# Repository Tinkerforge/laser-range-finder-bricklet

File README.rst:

Laser Range Finder Bricklet
===========================

This repository contains the firmware source code and the hardware design
files. The documentation generator configs can be found at
https://github.com/Tinkerforge/generators

Repository Content
------------------

software/:
 * examples/: Examples for all supported languages
 * build/: Compiled files
 * src/: Source code of firmware
 * Makefile: Makefile to build project

hardware/:
 * Contains KiCad project files and additionally schematics as PDF

datasheets/:
 * Contains datasheets for sensors and complex ICs that are used

Hardware
--------

The hardware is designed with the open source EDA Suite KiCad
(http://www.kicad.org). Before you are able to open the files,
you have to install the Tinkerforge kicad-libraries
(https://github.com/Tinkerforge/kicad-libraries). You can either clone
them directly in hardware/ or clone them in a separate folder and
symlink them into hardware/
(ln -s kicad_path/kicad-libraries project_path/hardware). After that you
can open the .pro file in hardware/ with KiCad and from there view and
modify the schematics and the PCB layout.

Software
--------

If you want to do your own Brick/Bricklet firmware development we highly
recommend that you use our build environment setup script and read the
tutorial (https://www.tinkerforge.com/en/doc/Tutorials/Tutorial_Build_Environment/Tutorial.html).

To compile the C code we recommend you to install the newest GNU Arm Embedded
Toolchain (https://launchpad.net/gcc-arm-embedded/+download).
You also need to install bricklib (https://github.com/Tinkerforge/bricklib)
and brickletlib (https://github.com/Tinkerforge/brickletlib).

You can either clone it directly in software/src/ or clone it in a
separate folder and symlink it into software/src/
(ln -s bricklib_path/bricklib project_path/software/src/ and
ln -s brickletlib_path/brickletlib project_path/software/src/).
Finally make sure to have CMake installed
(http://www.cmake.org/cmake/resources/software.html).

After that you can build the firmware by invoking make in software/.
The firmware (.bin) can then be found in software/build/ and uploaded
with brickv (click button "Flashing" on start screen).

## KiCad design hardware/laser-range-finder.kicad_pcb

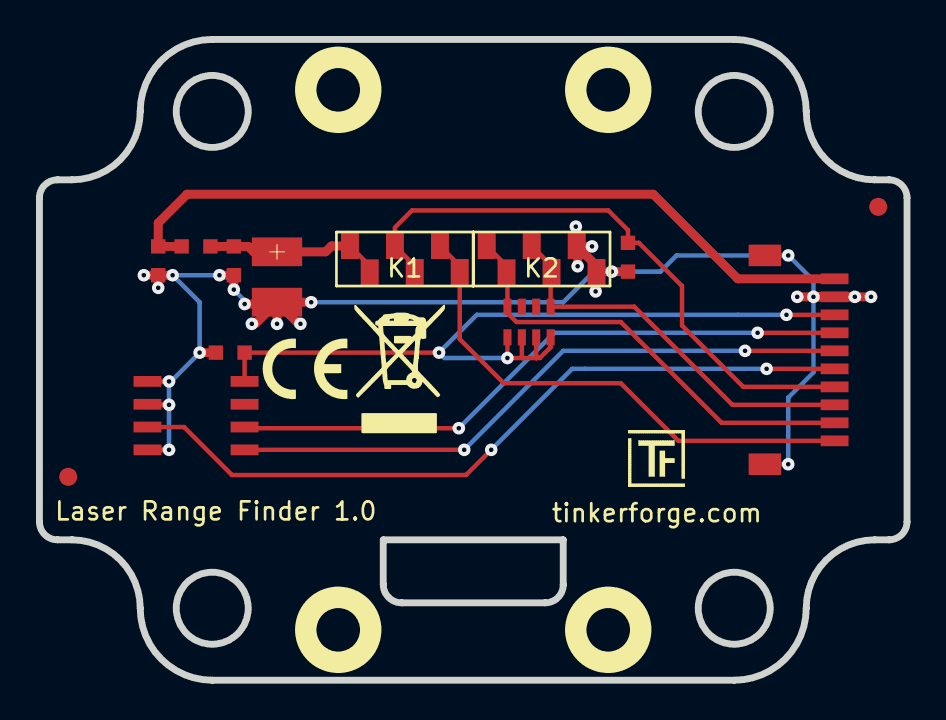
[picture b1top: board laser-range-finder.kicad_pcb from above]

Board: 2 copper layers, 48.2 x 35.6 mm, 18 parts (0 on the bottom side), 11 nets.

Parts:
C1: 100nF; C0603
C2, C3: 1µF; C0603
C4: 100µF; 3528-21
Fiducial_Mark: VAL**; Fiducial_Mark
Fiducial_Mark#2: VAL**; Fiducial_Mark
K1, K2: CONN_3; 9175-003
L1: FB-2; C0603
P1: CON-SENSOR
R1: 10k; R0603
RP1: 10k; 0603X4
U1: M24C64; SOIC8
U2, U3, U4, U5: DRILL; DRILL_NP
VAL: CE_5mm

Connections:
+5V: C2.1, L1.1, P1.1
ENABLE: K1.2, P1.7, R1.1
GND: C1.1, C2.2, C3.2, C4.2, K2.3, P1.2, P1.EP, R1.2, U1.1, U1.2, U1.4
MODE: K1.3, P1.10
unnamed: C3.1, C4.1, K1.1, L1.2
unnamed: P1.6, U1.3
SCL: P1.4, U1.6
SCL2: K2.1, P1.9, RP1.4
SDA: P1.5, U1.5
SDA2: K2.2, P1.8, RP1.1
VCC: C1.2, P1.3, RP1.5, RP1.6, RP1.7, RP1.8, U1.8

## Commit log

2015-03-05 Add stub implementation for initial API
2015-03-06 Add registers, move API around
2015-03-06 Add some mockup distance read code
2015-03-19 Add implementation for LRF
2015-03-26 add hardware files for laser range finder bricklet
2015-03-26 add schematic
2015-04-02 add fiducials
2015-04-02 drc rule check
2015-04-07 fix weee logo
2015-04-07 fix ce logo position
2015-04-16 Add .gitignore
2015-04-16 Change pin configuration to production version
2015-04-24 drc executed
2015-04-29 Add Python examples
2015-05-06 Add C examples
2015-05-06 Add C# examples
2015-05-06 Add Delphi examples
2015-05-06 Add Java examples
2015-05-07 Add JavaScript examples
2015-05-07 Add Perl examples
2015-05-07 Add missing laser enable and sleep
2015-05-07 Add PHP examples
2015-05-07 Add Ruby examples
2015-05-07 Add Shell examples
2015-05-07 Add VB.NET examples
2015-05-07 Add Matlab/Octave examples
2015-06-15 Some minor fixes on the MATLAB/Octave examples
2015-06-19 Add LabVIEW and Mathematica examples
    Also clean up other examples.
2015-06-24 Fix C examples for C99
2015-07-23 Make JavaScript browser example textarea readonly
2015-07-27 Cleanup Java and Python examples
2015-07-29 Reformat changelog
2015-08-03 fix typo
2015-08-04 ruby: Turn laser off on exit
2015-08-04 Add LIDAR-Lite v1 datasheet
2015-08-07 Use full device class name in Python examples
2015-08-07 Add missing time import in some Python examples
2015-08-12 Fix minor warnings in C/C++ examples
2015-08-12 Use millisleep helper in C/C++ examples
2015-08-18 Add missing DisableLaser calls to VB.NET examples
2015-08-18 Disable interrupts during I2C communication
    Fixes accidental incompatability with Servo Brick
2015-08-19 Whitespace
2015-08-24 Make sure interrupts are enabled after I2C
    communication in all cases
2015-09-09 Duplicate cmake call to fix bug during cmake creation
2015-09-30 Generator based example cleanup
2015-11-12 matlab: Fix callback handling for R2014a
    http://undocumentedmatlab.com/blog/matlab-callbacks-for-java-events-in-r2014a
2015-11-25 Include date and commit into changelog
2015-11-30 vbnet: Break long line
2016-02-11 Add full datasheet
2016-05-18 c: Add missing device destroy call
2016-07-01 Make the change UID comment more explicit
2017-01-31 Add sensor hardware version 3 specific API
    Note: This is WIP. We will change the 6 new modes to a more flexible configuration API.
2017-02-01 Add set/get_configuration API
2017-02-03 Refactor read_distance to save some more bytes of plugin size
2017-02-03 Add 2.0.3 changelog entry
2017-02-03 Add hash to changelog
2017-04-13 csharp: Adapt example
2017-04-21 shell: Adapt example
2017-06-02 octave: Use javaObject instead of deprecated java_new
2017-11-06 Fix edge cuts
2017-11-06 Add 3d information (final)
2017-11-06 Add 3d model (*.step & *.FCStd)
2017-11-30 Update examples from generator
2017-12-07 mathematica: Also generate .nb files
2018-01-26 c: Fine-tune printf format
2018-02-02 Update examples
2018-02-19 javascript: Close div tag correctly
2018-02-20 Cleanup KiCad libraries config
    Ensure LibDir=kicad-libraries and LibName1=tinkerforge.
    Remove special library.
2018-05-24 perl: Use strict in examples
2018-07-11 Add Makefile with docker support
2018-07-11 Remove obsolete generate_makefile scripts
2018-07-11 Update directory structure and build instructions
2018-11-06 Add rust examples
2018-11-07 rust: Accept host names for ip connection, fix naming inconsistencies
2018-11-07 rust: Rename callback receivers.
2018-12-14 Add go examples.
2018-12-18 go: Change import path.
2018-12-18 go: Change import path again.
2018-12-20 rust: Reformat examples.
2019-01-24 mqtt: Add examples.
2019-01-24 mqtt: Fix example header.
2019-01-24 mqtt: Remove executable bit in example permissions.
2019-01-24 go: Minor example fixes.
2019-01-24 mqtt: Minor example fixes.
2019-03-28 mqtt: Fix whitespace.
2019-08-22 c: Adapt to bindings changes
2020-01-13 examples: Use python3 input instead of python2 raw_input.
2020-01-13 examples: mqtt: Remove trailing whitespace.
2020-04-07 examples: rust: Always block when calling bindings functions.
2020-04-14 mqtt: Fix device name format
2021-10-25 Update KiCad link
    https://www.kicad.org/blog/2021/10/Avoid-links-to-former-kicad-domain/
2022-05-10 go: Fix format string
2022-07-06 Add license files.

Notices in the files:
hardware/laser-range-finder.kicad_pcb:
Licensed under CERN OHL v.1.1
Copyright (©) 2015, B.Nordmeyer
Copyright Tinkerforge GmbH 2015.
This documentation describes Open Hardware and is licensed under the
CERN OHL v. 1.1.
